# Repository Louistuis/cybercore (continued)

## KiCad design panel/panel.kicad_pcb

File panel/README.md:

# CyberCore status panel (rev 1.0)

The front panel of the CyberCore Console: a black 150 × 50 mm board with an ESP32-S3, a 16-LED RGB bar and a plug-in SPI display. It shows tokens/s, power and temperatures.
**This board is finished and orderable:** it's routed, DRC is clean, and every part is in stock at JLCPCB.

## What it does
- **Brain:** ESP32-S3-WROOM-1-N16R8 (Wi-Fi + native USB).
  - Data comes over USB from the machine itself: a small agent on the host writes stats to the USB serial port.
  - It can also pull data over Wi-Fi from a BMC (Redfish).
- **LED bar:** 16 × XL-5050RGBC-2812B (WS2812B type). A 74AHCT1G125 level-shifts the 3.3 V data line to 5 V.
  - Firmware caps the total current at ~400 mA so a USB 2.0 port can power it.
- **Display:** an 8-pin 2.54 mm header in Waveshare's module order (VCC GND DIN CLK CS DC RST BUSY).
  - It fits their SPI e-Paper modules (pin 8 = BUSY) and their SPI LCD modules (pin 8 = backlight), using the PH2.0 cable those modules ship with.
- **Power:** USB-C, 5 V, with a 1.5 A PTC fuse, ESD protection (USBLC6-2SC6) and an AMS1117 3.3 V regulator.
- **Also on board:** a Qwiic / STEMMA QT I2C port, PAGE / RESET / BOOT buttons, UART test pads and 4 × M3 holes.

## Board
- 2 layers, 1.6 mm, **black solder mask, white silk, ENIG**. JLCPCB standard rules (0.15 mm), with 2 USB necks at 0.125 mm.
- **Routing:** Freerouting, with GND poured on both layers and 98 stitching vias.
- **DRC:** 0 violations, 0 unconnected.
- **ERC:** 0 errors. There are 126 warnings because the symbols are embedded in the schematic, not in a library.

## Files
| File | What |
|---|---|
| `parts.py` | Netlist: every part, pin, LCSC number (checked 2026-11-16) and datasheet note |
| `make_panel.py` | Places parts and writes `panel.kicad_pcb` |
| `route.py` | `export` → Freerouting → `import` → `panel_routed.kicad_pcb` (+ black stackup) |
| `gen_sch.py` | Writes `panel.kicad_sch` from parts.py |
| `jlc_files.py` | `jlc/BOM.csv`, `jlc/CPL.csv`, `jlc/gerbers.zip` |

## Before ordering
1. In JLC's placement preview, check the rotation of every polarised part: U1-U4, D1-D16 and J1-J3.
2. Confirm the XL-5050RGBC-2812B pinout (1 VDD, 2 DOUT, 3 VSS, 4 DIN) against its datasheet.
3. Check the display pin order against the exact Waveshare module you buy.
4. Order settings: black mask, ENIG, 1.6 mm, 2 layers.

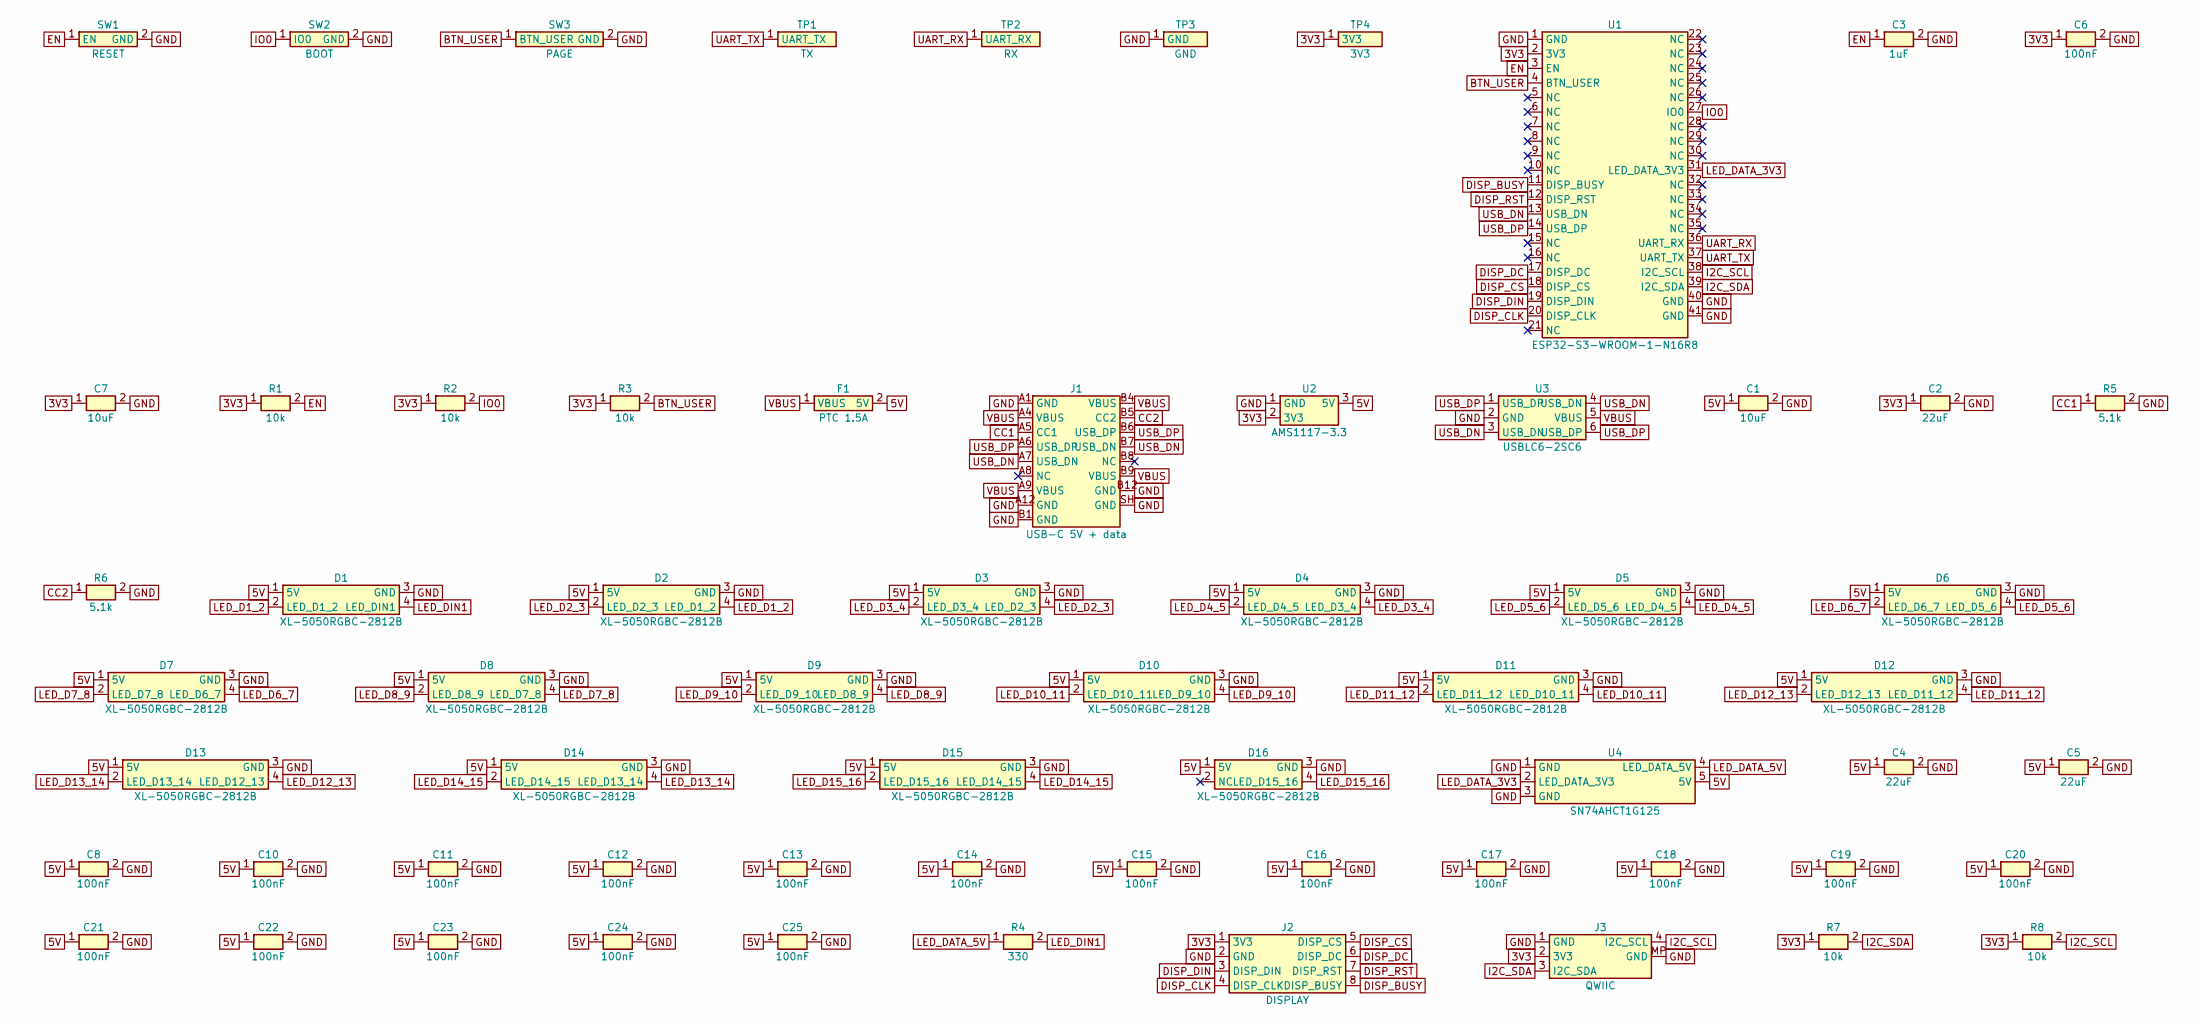
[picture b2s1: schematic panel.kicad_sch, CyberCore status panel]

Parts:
C1, C7: 10uF; C_0603_1608Metric; LCSC C19702
C2, C4, C5: 22uF; C_0805_2012Metric; LCSC C45783
C3: 1uF; C_0402_1005Metric; LCSC C52923
C6, C8, C10, C11, C12, C13, C14, C15, C16, C17, C18, C19, C20, C21, C22, C23, C24, C25: 100nF; C_0402_1005Metric; LCSC C1525
D1, D2, D3, D4, D5, D6, D7, D8, D9, D10, D11, D12, D13, D14, D15, D16: XL-5050RGBC-2812B; LED_WS2812B_PLCC4_5.0x5.0mm_P3.2mm; LCSC C2843785
F1: PTC 1.5A; Fuse_1206_3216Metric; LCSC C20802
J1: USB-C 5V + data; USB_C_Receptacle_HRO_TYPE-C-31-M-12; LCSC C165948
J2: DISPLAY; PinHeader_1x08_P2.54mm_Vertical; LCSC C32713274
J3: QWIIC; JST_SH_SM04B-SRSS-TB_1x04-1MP_P1.00mm_Horizontal; LCSC C160404
R1, R2, R3, R7, R8: 10k; R_0402_1005Metric; LCSC C25744
R4: 330; R_0402_1005Metric; LCSC C25104
R5, R6: 5.1k; R_0402_1005Metric; LCSC C25905
SW1: RESET; SW_Push_1P1T_XKB_TS-1187A; LCSC C318884
SW2: BOOT; SW_Push_1P1T_XKB_TS-1187A; LCSC C318884
SW3: PAGE; SW_Push_1P1T_XKB_TS-1187A; LCSC C318884
TP1: TX; TestPoint_Pad_D1.0mm
TP2: RX; TestPoint_Pad_D1.0mm
TP3: GND; TestPoint_Pad_D1.0mm
TP4: 3V3; TestPoint_Pad_D1.0mm
U1: ESP32-S3-WROOM-1-N16R8; ESP32-S3-WROOM-1; LCSC C2913202
U2: AMS1117-3.3; SOT-223-3_TabPin2; LCSC C6186
U3: USBLC6-2SC6; SOT-23-6; LCSC C7519
U4: SN74AHCT1G125; SOT-23-5; LCSC C7484

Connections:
3V3: C2.1, C6.1, C7.1, J2.1 (3V3), J3.2 (3V3), R1.1, R2.1, R3.1, R7.1, R8.1, TP4.1, U1.2 (3V3), U2.2 (3V3)
5V: C1.1, C4.1, C5.1, C8.1, C10.1, C11.1, C12.1, C13.1, C14.1, C15.1, C16.1, C17.1, C18.1, C19.1, C20.1, C21.1, C22.1, C23.1, C24.1, C25.1, D1.1 (5V), D2.1 (5V), D3.1 (5V), D4.1 (5V), D5.1 (5V), D6.1 (5V), D7.1 (5V), D8.1 (5V), D9.1 (5V), D10.1 (5V), D11.1 (5V), D12.1 (5V), D13.1 (5V), D14.1 (5V), D15.1 (5V), D16.1 (5V), F1.2 (5V), U2.3 (5V), U4.5 (5V)
BTN_USER: R3.2, SW3.1 (BTN_USER), U1.4 (BTN_USER)
CC1: J1.A5 (CC1), R5.1
CC2: J1.B5 (CC2), R6.1
DISP_BUSY: J2.8 (DISP_BUSY), U1.11 (DISP_BUSY)
DISP_CLK: J2.4 (DISP_CLK), U1.20 (DISP_CLK)
DISP_CS: J2.5 (DISP_CS), U1.18 (DISP_CS)
DISP_DC: J2.6 (DISP_DC), U1.17 (DISP_DC)
DISP_DIN: J2.3 (DISP_DIN), U1.19 (DISP_DIN)
DISP_RST: J2.7 (DISP_RST), U1.12 (DISP_RST)
EN: C3.1, R1.2, SW1.1 (EN), U1.3 (EN)
GND: C1.2, C2.2, C3.2, C4.2, C5.2, C6.2, C7.2, C8.2, C10.2, C11.2, C12.2, C13.2, C14.2, C15.2, C16.2, C17.2, C18.2, C19.2, C20.2, C21.2, C22.2, C23.2, C24.2, C25.2, D1.3 (GND), D2.3 (GND), D3.3 (GND), D4.3 (GND), D5.3 (GND), D6.3 (GND), D7.3 (GND), D8.3 (GND), D9.3 (GND), D10.3 (GND), D11.3 (GND), D12.3 (GND), D13.3 (GND), D14.3 (GND), D15.3 (GND), D16.3 (GND), J1.A1 (GND), J1.A12 (GND), J1.B1 (GND), J1.B12 (GND), J1.SH (GND), J2.2 (GND), J3.1 (GND), J3.MP (GND), R5.2, R6.2, SW1.2 (GND), SW2.2 (GND), SW3.2 (GND), TP3.1, U1.1 (GND), U1.40 (GND), U1.41 (GND), U2.1 (GND), U3.2 (GND), U4.1 (GND), U4.3 (GND)
I2C_SCL: J3.4 (I2C_SCL), R8.2, U1.38 (I2C_SCL)
I2C_SDA: J3.3 (I2C_SDA), R7.2, U1.39 (I2C_SDA)
IO0: R2.2, SW2.1 (IO0), U1.27 (IO0)
LED_D1_2: D1.2 (LED_D1_2), D2.4 (LED_D1_2)
LED_D2_3: D2.2 (LED_D2_3), D3.4 (LED_D2_3)
LED_D3_4: D3.2 (LED_D3_4), D4.4 (LED_D3_4)
LED_D4_5: D4.2 (LED_D4_5), D5.4 (LED_D4_5)
LED_D5_6: D5.2 (LED_D5_6), D6.4 (LED_D5_6)
LED_D6_7: D6.2 (LED_D6_7), D7.4 (LED_D6_7)
LED_D7_8: D7.2 (LED_D7_8), D8.4 (LED_D7_8)
LED_D8_9: D8.2 (LED_D8_9), D9.4 (LED_D8_9)
LED_D9_10: D9.2 (LED_D9_10), D10.4 (LED_D9_10)
LED_D10_11: D10.2 (LED_D10_11), D11.4 (LED_D10_11)
LED_D11_12: D11.2 (LED_D11_12), D12.4 (LED_D11_12)
LED_D12_13: D12.2 (LED_D12_13), D13.4 (LED_D12_13)
LED_D13_14: D13.2 (LED_D13_14), D14.4 (LED_D13_14)
LED_D14_15: D14.2 (LED_D14_15), D15.4 (LED_D14_15)
LED_D15_16: D15.2 (LED_D15_16), D16.4 (LED_D15_16)
LED_DATA_3V3: U1.31 (LED_DATA_3V3), U4.2 (LED_DATA_3V3)
LED_DATA_5V: R4.1, U4.4 (LED_DATA_5V)
LED_DIN1: D1.4 (LED_DIN1), R4.2
UART_RX: TP2.1, U1.36 (UART_RX)
UART_TX: TP1.1, U1.37 (UART_TX)
USB_DN: J1.A7 (USB_DN), J1.B7 (USB_DN), U1.13 (USB_DN), U3.3 (USB_DN), U3.4 (USB_DN)
USB_DP: J1.A6 (USB_DP), J1.B6 (USB_DP), U1.14 (USB_DP), U3.1 (USB_DP), U3.6 (USB_DP)
VBUS: F1.1 (VBUS), J1.A4 (VBUS), J1.A9 (VBUS), J1.B4 (VBUS), J1.B9 (VBUS), U3.5 (VBUS)

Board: 2 copper layers, 67 parts (0 on the bottom side), 39 nets, no tracks yet.

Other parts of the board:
H1, H2, H3, H4: M3; MountingHole_3.2mm_M3

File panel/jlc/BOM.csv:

Comment,Designator,Footprint,LCSC Part #
10uF,"C1,C7",C_0603_1608Metric,C19702
100nF,"C10,C11,C12,C13,C14,C15,C16,C17,C18,C19,C20,C21,C22,C23,C24,C25,C6,C8",C_0402_1005Metric,C1525
22uF,"C2,C4,C5",C_0805_2012Metric,C45783
1uF,C3,C_0402_1005Metric,C52923
XL-5050RGBC-2812B,"D1,D10,D11,D12,D13,D14,D15,D16,D2,D3,D4,D5,D6,D7,D8,D9",LED_WS2812B_PLCC4_5.0x5.0mm_P3.2mm,C2843785
PTC 1.5A,F1,Fuse_1206_3216Metric,C20802
USB-C 5V + data,J1,USB_C_Receptacle_HRO_TYPE-C-31-M-12,C165948
DISPLAY,J2,PinHeader_1x08_P2.54mm_Vertical,C32713274
QWIIC,J3,JST_SH_SM04B-SRSS-TB_1x04-1MP_P1.00mm_Horizontal,C160404
10k,"R1,R2,R3,R7,R8",R_0402_1005Metric,C25744
330,R4,R_0402_1005Metric,C25104
5.1k,"R5,R6",R_0402_1005Metric,C25905
RESET,SW1,SW_Push_1P1T_XKB_TS-1187A,C318884
BOOT,SW2,SW_Push_1P1T_XKB_TS-1187A,C318884
PAGE,SW3,SW_Push_1P1T_XKB_TS-1187A,C318884
ESP32-S3-WROOM-1-N16R8,U1,ESP32-S3-WROOM-1,C2913202
AMS1117-3.3,U2,SOT-223-3_TabPin2,C6186
USBLC6-2SC6,U3,SOT-23-6,C7519
SN74AHCT1G125,U4,SOT-23-5,C7484
